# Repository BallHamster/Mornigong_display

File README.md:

# Mornigong_display
Welcome all to my project mornigong, and this part of it: Mornigong display.
This project uses a cheap aliexpress eink raw screen (Image below), a raspberry pi zero 2 w, and a custom made driver board for the screen.

## The board I made

This is the schematic of my board. The connector is an FPC 24 pin cable, carrying SPI data, and power for the screen. As the screen has no power onboard, I had to make the power boost circuit too. It is largely based on the official Waveshare esp32 driver board V3.(Source: https://files.waveshare.com/wiki/E-Paper-ESP32-Driver-Board/E-Paper_ESP32_Driver_Board_V3.pdf?)

This is the final PCB layout, and routing. Everything is close to the components it needs to be. (Or I hope so...)

This is a help table for the resistor voltages with the reference numbers.

This is the 3d render of the board. It is designed to be a hat for the zero 2 w.

## Software
The software I used, is as open-source project, called Inkypi, made by Faith Ak. (https://github.com/fatihak/InkyPi)
### Installation guide
- Write an image of an official Raspberry pi OS lite 64bit on your sdcard/usb drive.
- Clone the repository: ```git clone https://github.com/fatihak/InkyPi.git```
- Navigate to the project directory: ```cd InkyPi```
- Run the installation script with sudo: ```sudo bash install/install.sh -W epd7in5b_HD``` (as the screen I am using is an exact copy of the Waveshare 7.5 in model.)
- Restart your pi
- Head to https://<your_pi_ip> for configuration and first time setup.

### Example software
There is a copy of an example software in this repo, called "ex_software.bin" which is an image of the directory of Inkypi on my RPI with my screen model.

# Important
- This project is not tested yet, it only works in theory.
- All the credits go to Faith ak, for the Inkypi software.
# BOM
| Reference number | Description | LCSC part number | Needed number | Minimum order number | Price of minimal order number/needed number ($) | link |
|---|---|---|---|---|---|---|
| C7, C8, C10, C12, C13, C14, C15, C16, C17, C18, C19 | 1 uF 50 V X7R 0805 MLCC, Kyocera AVX 08055C105KAT2A | C2167382 | 11 | 15 | 2.5 | https://www.lcsc.com/product-detail/C2167382.html |
| C20 | 10 uF 25 V X5R 0805 MLCC, Samsung CL21A106KAYNNNE | C15850 | 1 | 20 | 0.88 | https://www.lcsc.com/product-detail/C15850.html |
| C21 | 100 nF 50 V X7R 0805 MLCC, Samsung CL21B104KBCNNNC | C1711 | 1 | 20 | 0.28 | https://www.lcsc.com/product-detail/C1711.html |
| D1, D2, D3 | Schottky diode 30 V 0.5 A SOD-123, onsemi MBR0530T1G | C82046 | 3 | 10 | 0.63 | https://www.lcsc.com/product-detail/C82046.html |
| L1 | 47 uH shielded inductor 4.8x4.8x2.8 mm, Bourns SRR4028-470Y | C2041925 | 1 | 1 | 0.43 | https://www.lcsc.com/product-detail/C2041925.html |
| Q1 | N-MOSFET 30 V SOT-323, Vishay Si1308EDL-T1-GE3 (Si1304BDL helyett) | C469327 | 1 | 5 | 1.31 | https://www.lcsc.com/product-detail/C469327.html |
| R1 | 0.47 ohm 1% 0805, Yageo RL0805FR-070R47L | C705493 | 1 | 50 | 0.73 | https://www.lcsc.com/product-detail/C705493.html |
| R2 | 100 kohm 1% 0805, Yageo RC0805FR-07100KL | C96346 | 1 | 100 | 0.47 | https://www.lcsc.com/product-detail/C96346.html |
| R5 | 3 ohm 1% 0805, Yageo RC0805FR-073RL | C137528 | 1 | 50 | 0.94 | https://www.lcsc.com/product-detail/C137528.html |
| U1 | FPC connector 24 pin 0.5 mm, SHOU HAN FPC 0.5-24P | C6364666 | 1 | 5 | 0.86 | https://www.lcsc.com/product-detail/C6364666.html |
| J1 | 2x20 pin 2.54 mm pin header | C2977589 | 1 | 5 | 1.62 | https://www.lcsc.com/product-detail/C2977589.html |
| - | Screen | - | 1 | 1 | 15 | https://www.aliexpress.com/item/1005006901112592.html |
| U2 | Raspberry pi zero 2 w | - | 1 | 1 | 20 | https://malnapc.hu/raspberry-pi-zero-2-w?src=raspberrypi |

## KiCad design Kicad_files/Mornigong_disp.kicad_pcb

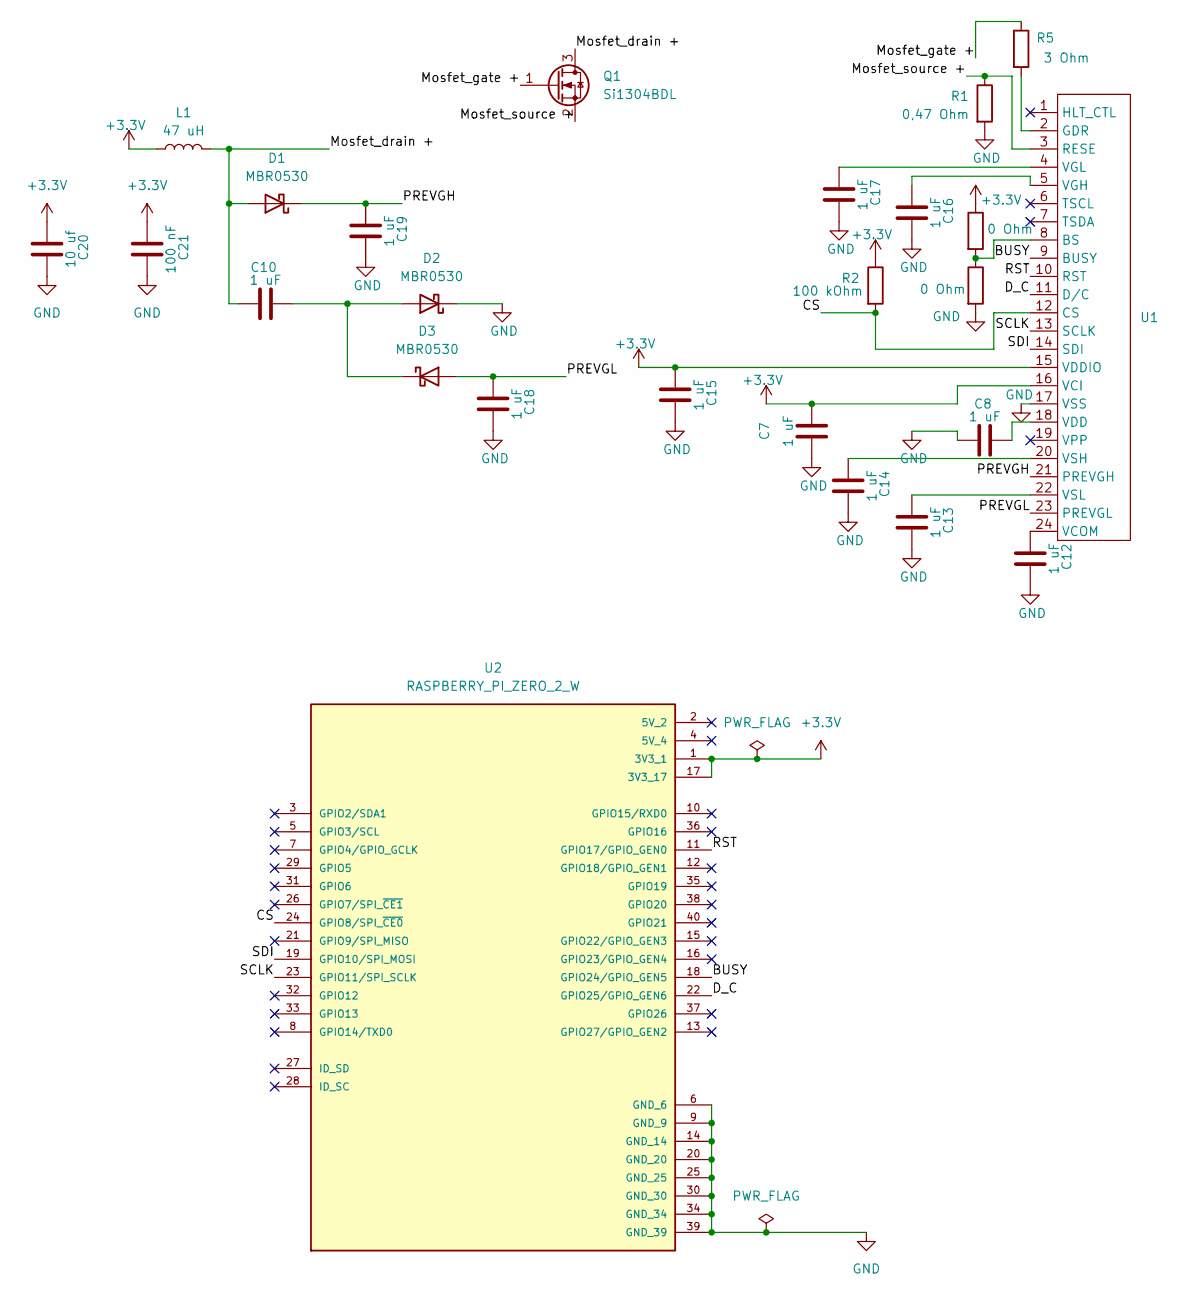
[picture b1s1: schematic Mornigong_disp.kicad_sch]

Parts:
C7, C8, C10, C12, C13, C14, C15, C16, C17, C18, C19: 1 uF; C_0805_2012Metric_Pad1.18x1.45mm_HandSolder
C20: 10 uf; C_0805_2012Metric_Pad1.18x1.45mm_HandSolder
C21: 100 nF; C_0805_2012Metric_Pad1.18x1.45mm_HandSolder
D1, D2, D3: MBR0530; D_SOD-123
L1: 47 uH; SRR4028
Q1: Si1304BDL; SOT-323_SC-70
R1: 0,47 Ohm; R_0805_2012Metric_Pad1.20x1.40mm_HandSolder
R2: 100 kOhm; R_0805_2012Metric_Pad1.20x1.40mm_HandSolder
R3, R4: 0 Ohm; R_0805_2012Metric_Pad1.20x1.40mm_HandSolder
R5: 3 Ohm; R_0805_2012Metric_Pad1.20x1.40mm_HandSolder
U1: Amphenol_F32Q-1A7x1-11024_1x24-1MP_P0.5mm_Horizontal
U2: RASPBERRY_PI_ZERO_2_W; MODULE_RASPBERRY_PI_ZERO_2_W; PARTREV April 2024

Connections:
+3.3V: C7.2, C15.1, C20.1, C21.1, L1.1, R2.1, R4.1, U1.15 (VDDIO), U1.16 (VCI), U2.1 (3V3_1), U2.17 (3V3_17)
/BUSY: U1.9 (BUSY), U2.18 (GPIO24/GPIO_GEN5)
/CS: R2.2, U1.12 (CS), U2.24 (GPIO8/SPI_~CE0)
/D_C: U1.11 (D/C), U2.22 (GPIO25/GPIO_GEN6)
/Mosfet_drain +: C10.1, D1.2 (A), L1.2, Q1.3 (D)
/Mosfet_gate +: Q1.1 (G), R5.1
/Mosfet_source +: Q1.2 (S), R1.1, U1.3 (RESE)
/PREVGH: C19.1, D1.1 (K), U1.21 (PREVGH)
/PREVGL: C18.1, D3.2 (A), U1.23 (PREVGL)
/RST: U1.10 (RST), U2.11 (GPIO17/GPIO_GEN0)
/SCLK: U1.13 (SCLK), U2.23 (GPIO11/SPI_SCLK)
/SDI: U1.14 (SDI), U2.19 (GPIO10/SPI_MOSI)
GND: C7.1, C8.1, C12.2, C13.2, C14.2, C15.2, C16.2, C17.2, C18.2, C19.2, C20.2, C21.2, D2.1 (K), R1.2, R3.2, U1.17 (VSS), U2.6 (GND_6), U2.9 (GND_9), U2.14 (GND_14), U2.20 (GND_20), U2.25 (GND_25), U2.30 (GND_30), U2.34 (GND_34), U2.39 (GND_39)
unnamed: C10.2, D2.2 (A), D3.1 (K)
unnamed: R3.1, R4.2, U1.8 (BS)
unnamed: R5.2, U1.2 (GDR)
unnamed: C12.1, U1.24 (VCOM)
unnamed: C8.2, U1.18 (VDD)
unnamed: C16.1, U1.5 (VGH)
unnamed: C17.1, U1.4 (VGL)
unnamed: C14.1, U1.20 (VSH)
unnamed: C13.1, U1.22 (VSL)

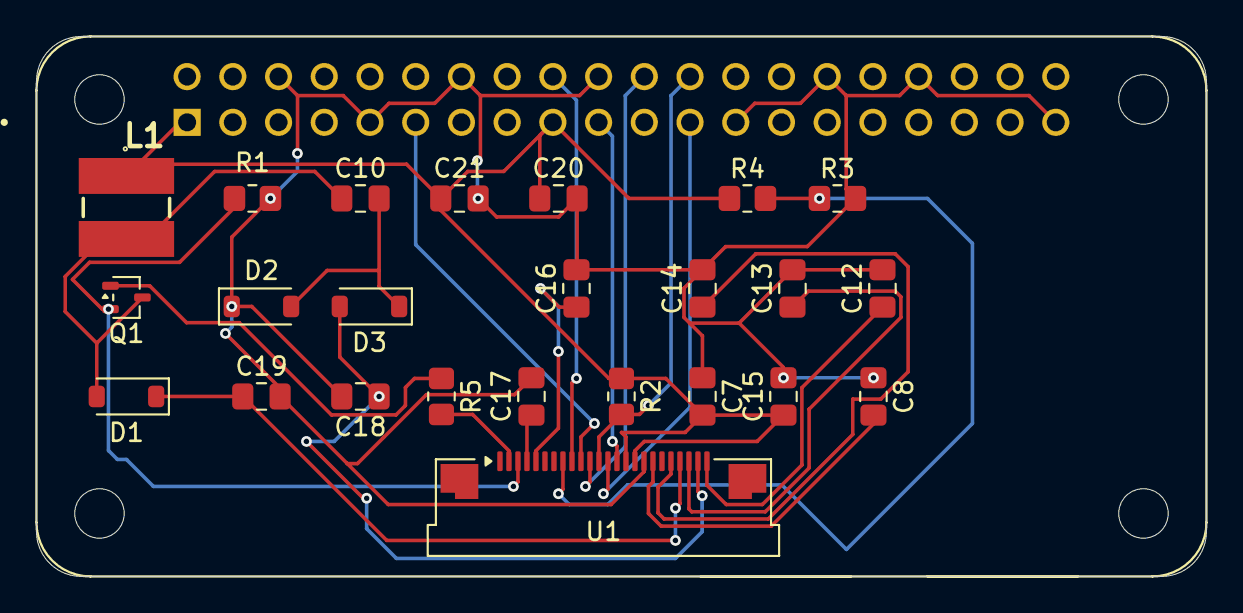
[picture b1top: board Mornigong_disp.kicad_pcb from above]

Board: 2 copper layers, 65.0 x 30.0 mm, 25 parts (0 on the bottom side), 22 nets.
